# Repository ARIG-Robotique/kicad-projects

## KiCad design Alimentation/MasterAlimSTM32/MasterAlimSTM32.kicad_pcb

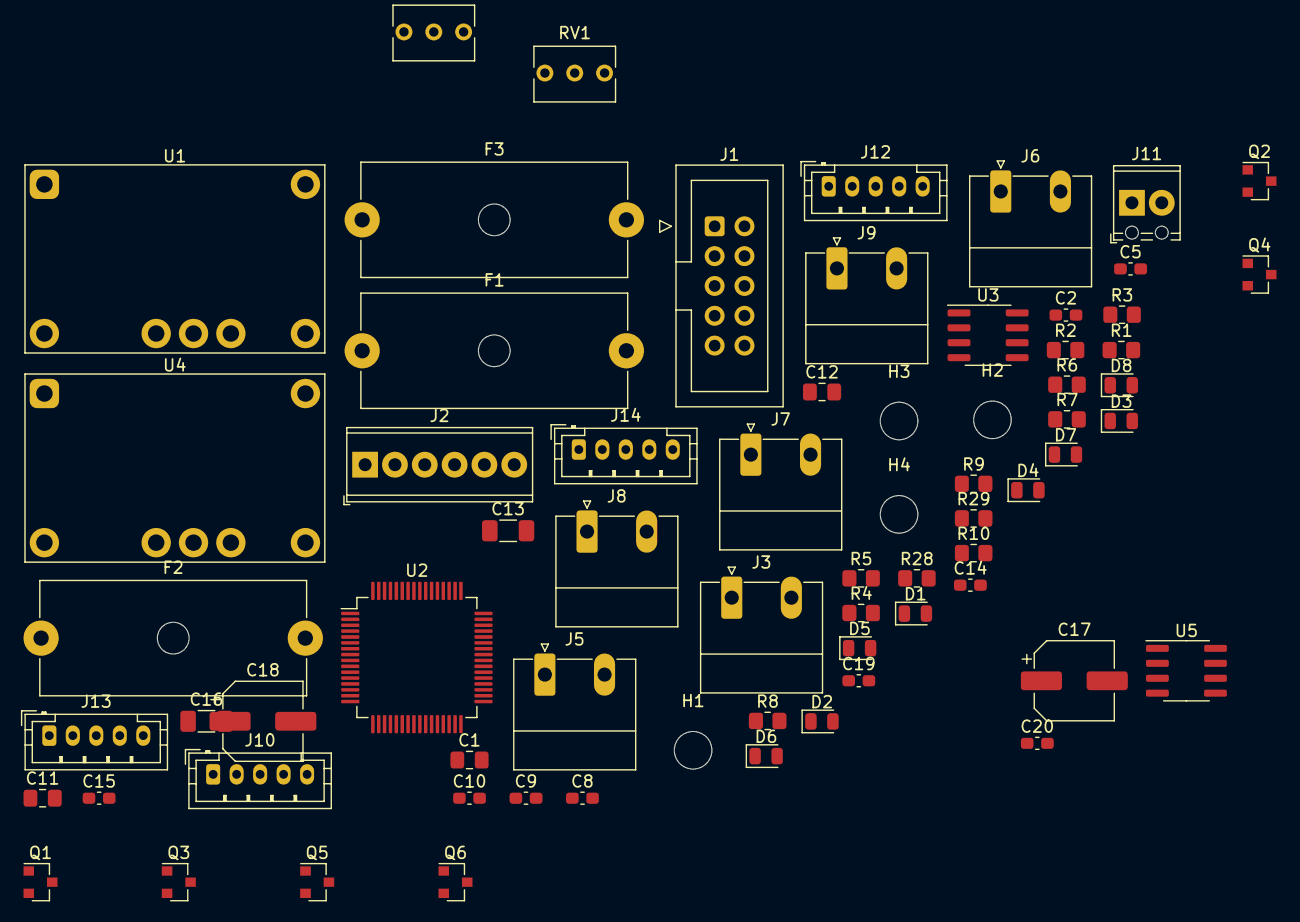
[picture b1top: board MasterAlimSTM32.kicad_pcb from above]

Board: 2 copper layers, 69 parts (0 on the bottom side), 39 nets, no tracks yet.

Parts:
C1: 4.7u; C_0805_2012Metric_Pad1.18x1.45mm_HandSolder
C2, C5, C8, C9, C10, C15, C20: 100n; C_0603_1608Metric_Pad1.08x0.95mm_HandSolder
C11, C12: 2.2u; C_0805_2012Metric_Pad1.18x1.45mm_HandSolder
C13, C16: 2.2u; C_1206_3216Metric_Pad1.33x1.80mm_HandSolder
C14, C19: 1n; C_0603_1608Metric_Pad1.08x0.95mm_HandSolder
C17, C18: 100u; CP_Elec_6.3x5.4
D1: AU; LED_0805_2012Metric
D2: 5V; LED_0805_2012Metric
D3: T1; LED_0805_2012Metric
D4: T2; LED_0805_2012Metric
D5: T3; LED_0805_2012Metric
D6: T4; LED_0805_2012Metric
D7: 3.3V; LED_0805_2012Metric
D8: Heart Beat; LED_0805_2012Metric
F1: 10A; Fuseholder_Cylinder-5x20mm_Schurter_0031_8201_Horizontal_Op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
F2, F3: 3A; Fuseholder_Cylinder-5x20mm_Schurter_0031_8201_Horizontal_Op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
H1, H2, H3, H4: MountingHole; MountingHole_3.2mm_M3
J1: Ext-Con; IDC-Header_2x05_P2.54mm_Vertical
J2: 5V; TerminalBlock_Phoenix_MPT-0,5-6-2.54_1x06_P2.54mm_Horizontal
J3: Bat. IN; PhoenixContact_MC_1,5_2-G-5.08_1x02_P5.08mm_Horizontal
J5: Direct Out; PhoenixContact_MC_1,5_2-G-5.08_1x02_P5.08mm_Horizontal
J6: Reg 1; PhoenixContact_MC_1,5_2-G-5.08_1x02_P5.08mm_Horizontal
J7: Reg 2; PhoenixContact_MC_1,5_2-G-5.08_1x02_P5.08mm_Horizontal
J8: Reg 3; PhoenixContact_MC_1,5_2-G-5.08_1x02_P5.08mm_Horizontal
J9: Reg 4; PhoenixContact_MC_1,5_2-G-5.08_1x02_P5.08mm_Horizontal
J10: Interf-Reg1; JST_PH_B5B-PH-K_1x05_P2.00mm_Vertical
J11: AU Logic; TerminalBlock_Phoenix_MPT-0,5-2-2.54_1x02_P2.54mm_Horizontal
J12: Interf-Reg2; JST_PH_B5B-PH-K_1x05_P2.00mm_Vertical
J13: Interf-Reg3; JST_PH_B5B-PH-K_1x05_P2.00mm_Vertical
J14: Interf-Reg4; JST_PH_B5B-PH-K_1x05_P2.00mm_Vertical
Q1, Q2, Q3, Q4, Q5, Q6: BSS138; SOT-23
R1, R8: 10k; R_0805_2012Metric_Pad1.20x1.40mm_HandSolder
R2: 220; R_0805_2012Metric_Pad1.20x1.40mm_HandSolder
R3: 280; R_0805_2012Metric_Pad1.20x1.40mm_HandSolder
R4, R5, R6, R7: 180; R_0805_2012Metric_Pad1.20x1.40mm_HandSolder
R9: 150; R_0805_2012Metric_Pad1.20x1.40mm_HandSolder
R10: 1k5; R_0805_2012Metric_Pad1.20x1.40mm_HandSolder
R28: 820k; R_0805_2012Metric_Pad1.20x1.40mm_HandSolder
R29: 130k; R_0805_2012Metric_Pad1.20x1.40mm_HandSolder
RV1, RV2: 1M; Potentiometer_Bourns_3266Y_Vertical
U1, U4: PTN78060W_EUW-7; Texas_EUW_R-PDSS-T7_THT
U2: STM32F405RGTx; LQFP-64_10x10mm_P0.5mm
U3, U5: ACS712xLCTR-20A; SOIC-8_3.9x4.9mm_P1.27mm

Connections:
+3V3: C1.1, C2.2, C5.2, C8.2, C9.2, C10.2, F3.2, J1.3, J2.3, J2.4, Q1.1, Q2.1, Q3.1, Q4.1, Q5.1, Q6.1, R1.1, R2.1, R4.1, R5.1, R6.1, R7.1, R9.1, U2.1, U2.19, U2.32, U2.48, U2.64
+5V: C15.2, C20.2, F2.1, J1.1, J2.1, J2.2, J10.1, J12.1, J13.1, J14.1, R3.1, U3.8, U5.8
+BATT: C13.1, C16.1, F1.1, J5.2, J6.2, J7.2, J8.2, J9.2, RV1.1, RV2.1, U1.2, U4.2
/ANA_BAT_VOLT_5: R28.2, R29.1
/AU_33: D1.1, J11.1, R1.2, U2.41
/BAT_IN: F1.2, R28.1, U3.3, U3.4
/BOOT0: R8.1, U2.60
/EN_T1_5: J10.2, Q3.3
/EN_T1_33: D3.1, Q3.2, U2.33
/EN_T2_5: J12.2, Q4.3
/EN_T2_33: D4.1, Q4.2, U2.34
/EN_T3_5: J13.2, Q5.3
/EN_T3_33: D5.1, Q5.2, U2.35
/EN_T4_5: J14.2, Q6.3
/EN_T4_33: D6.1, Q6.2, U2.36
/HEART_BEAT_33: D8.2, U2.43
/SCL_5: J1.10, Q1.3
/SCL_33: J1.8, Q1.2, U2.58
/SDA_5: J1.9, Q2.3
/SDA_33: J1.7, Q2.2, U2.59
/VO_5: C17.1, U1.5, U1.6, U5.1, U5.2
GND: C1.2, C2.1, C5.1, C8.1, C9.1, C10.1, C11.2, C12.2, C13.2, C14.2, C15.1, C16.2, C17.2, C18.2, C19.2, C20.1, D2.1, D7.1, J1.2, J1.4, J2.5, J2.6, J3.1, J5.1, J6.1, J7.1, J8.1, J9.1, J10.5, J11.2, J12.5, J13.5, J14.5, R10.2, R29.2, RV1.3, RV2.3, U1.1, U1.7, U2.12, U2.18, U2.63, U3.5, U4.1, U4.7, U5.5
unnamed: C11.1, U2.31
unnamed: C12.1, U2.47
unnamed: C14.1, U3.6
unnamed: C18.1, F3.1, U4.5, U4.6
unnamed: C19.1, U5.6
unnamed: D1.2, R2.2
unnamed: D2.2, R3.2
unnamed: D3.2, R4.2
unnamed: D4.2, R5.2
unnamed: D5.2, R6.2
unnamed: D6.2, R7.2
unnamed: D7.2, R9.2
unnamed: D8.1, R10.1
unnamed: F2.2, U5.3, U5.4
unnamed: J3.2, U3.1, U3.2
unnamed: RV1.2, U1.4
unnamed: RV2.2, U4.4

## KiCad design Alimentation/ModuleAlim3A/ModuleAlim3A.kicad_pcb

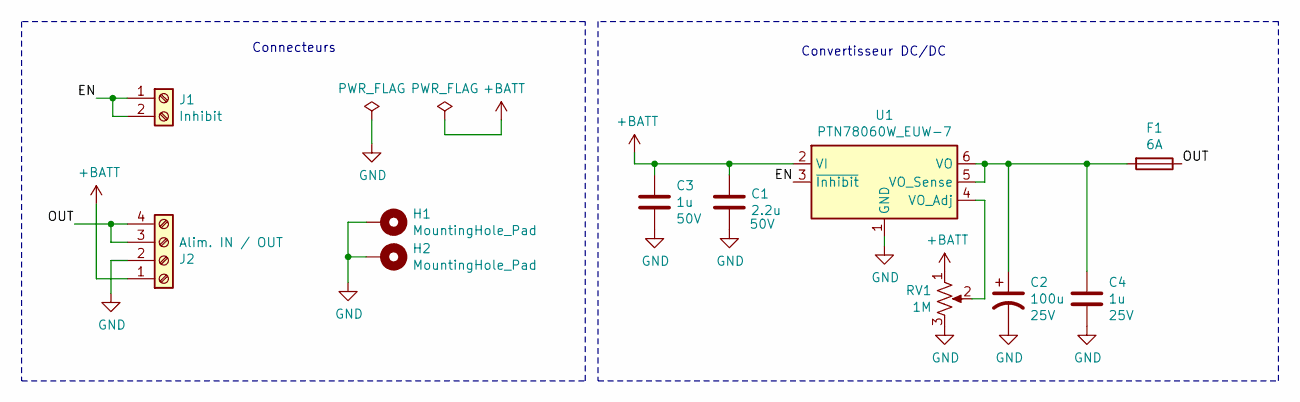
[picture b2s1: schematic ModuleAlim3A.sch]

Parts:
C1: 2.2u; C_1206_3216Metric_Pad1.33x1.80mm_HandSolder; LCSC Part C50254
C2: 100u; CP_Elec_6.3x7.7; LCSC Part C176675
C3: 1u; C_0805_2012Metric_Pad1.18x1.45mm_HandSolder; LCSC Part C28323
C4: 1u; C_0402_1005Metric_Pad0.74x0.62mm_HandSolder; LCSC Part C52923
F1: 6A; Fuseholder_Cylinder-5x20mm_Schurter_0031_8201_Horizontal_Op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; JLCPCB BOM 0
H1, H2: MountingHole_Pad; MountingHole_3.2mm_M3_Pad_Via; JLCPCB BOM 0
J1: Inhibit; TerminalBlock_Phoenix_MPT-0,5-2-2.54_1x02_P2.54mm_Horizontal; JLCPCB BOM 0
J2: Alim. IN / OUT; TerminalBlock_Phoenix_MKDS-1,5-4-5.08_1x04_P5.08mm_Horizont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; JLCPCB BOM 0
RV1: 1M; Potentiometer_Bourns_3296W_Vertical; JLCPCB BOM 0
U1: PTN78060W_EUW-7; Texas_EUW_R-PDSS-T7_THT; JLCPCB BOM 0

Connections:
+BATT: C1.1, C3.1, J2.1, RV1.1, U1.2 (VI)
/EN: J1.1, J1.2, U1.3 (~Inhibit)
/OUT: F1.1, J2.3, J2.4
GND: C1.2, C2.2, C3.2, C4.2, H1.1, H2.1, J2.2, RV1.3, U1.1 (GND), U1.7 (GND)
unnamed: C2.1, C4.1, F1.2, U1.5 (VO_Sense), U1.6 (VO)
unnamed: RV1.2, U1.4 (VO_Adj)

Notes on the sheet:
Convertisseur DC/DC
Connecteurs

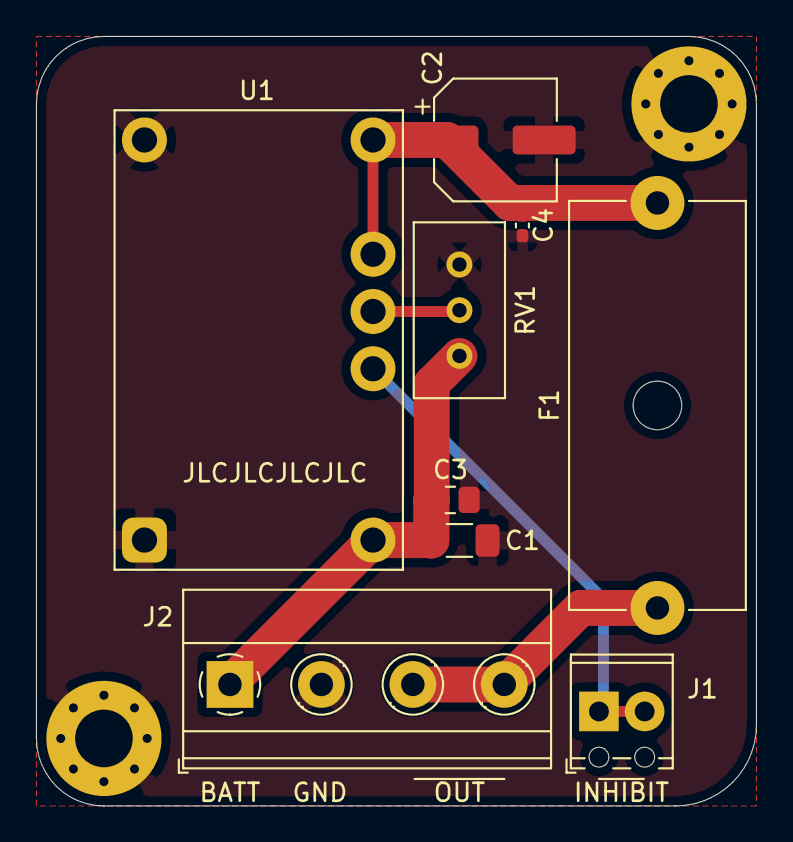
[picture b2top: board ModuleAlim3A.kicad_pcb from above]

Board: 2 copper layers, 40.0 x 42.8 mm, 11 parts (0 on the bottom side), 6 nets.

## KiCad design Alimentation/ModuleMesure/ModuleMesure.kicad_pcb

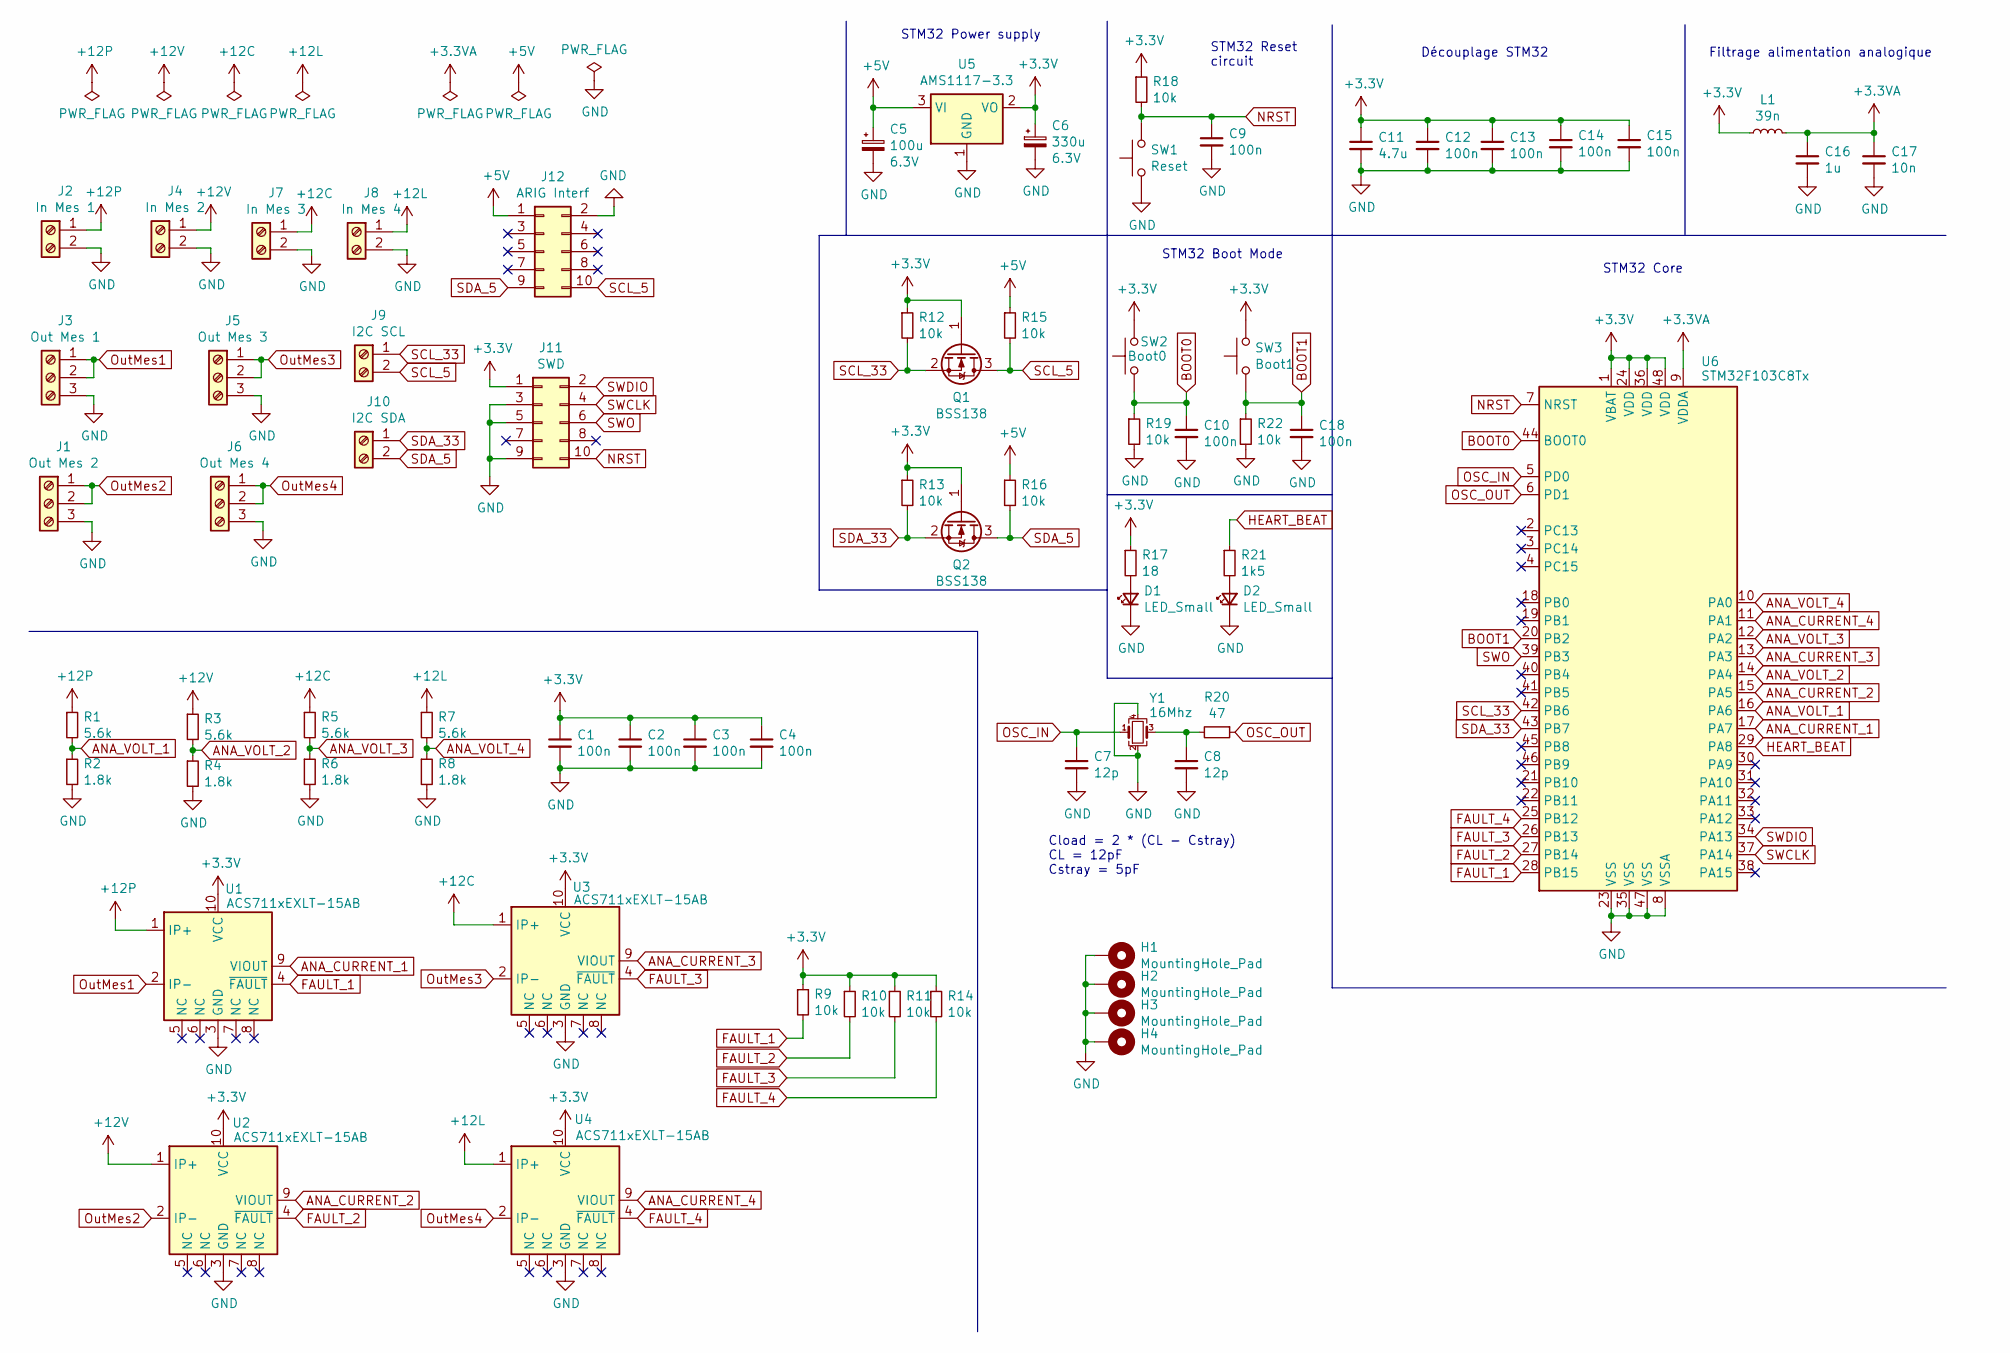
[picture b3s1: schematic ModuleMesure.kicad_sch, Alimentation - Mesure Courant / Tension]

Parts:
C1, C2, C3, C4, C9, C10, C12, C13, C14, C15, C18: 100n; C_0402_1005Metric_Pad0.74x0.62mm_HandSolder; LCSC Part C541405
C5: 100u; CP_Elec_5x5.4; LCSC Part C72472
C6: 330u; CP_Elec_6.3x7.7; LCSC Part C58276
C7, C8: 12p; C_0402_1005Metric_Pad0.74x0.62mm_HandSolder
C11: 4.7u; C_0402_1005Metric_Pad0.74x0.62mm_HandSolder; LCSC Part C87147
C16: 1u; C_0402_1005Metric_Pad0.74x0.62mm_HandSolder; LCSC Part C87144
C17: 10n; C_0402_1005Metric_Pad0.74x0.62mm_HandSolder; LCSC Part C309453
D1, D2: LED_Small; LED_0805_2012Metric_Pad1.15x1.40mm_HandSolder
H1, H2, H3, H4: MountingHole_Pad; MountingHole_3.2mm_M3_Pad_Via
J1: Out Mes 2; TerminalBlock_Phoenix_MKDS-1,5-3-5.08_1x03_P5.08mm_Horizont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
J2: In Mes 1; TerminalBlock_Phoenix_MKDS-1,5-2-5.08_1x02_P5.08mm_Horizont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
J3: Out Mes 1; TerminalBlock_Phoenix_MKDS-1,5-3-5.08_1x03_P5.08mm_Horizont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
J4: In Mes 2; TerminalBlock_Phoenix_MKDS-1,5-2-5.08_1x02_P5.08mm_Horizont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
J5: Out Mes 3; TerminalBlock_Phoenix_MKDS-1,5-3-5.08_1x03_P5.08mm_Horizont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
J6: Out Mes 4; TerminalBlock_Phoenix_MKDS-1,5-3-5.08_1x03_P5.08mm_Horizont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
J7: In Mes 3; TerminalBlock_Phoenix_MKDS-1,5-2-5.08_1x02_P5.08mm_Horizont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
J8: In Mes 4; TerminalBlock_Phoenix_MKDS-1,5-2-5.08_1x02_P5.08mm_Horizont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
J9: I2C SCL; TerminalBlock_Phoenix_MPT-0,5-2-2.54_1x02_P2.54mm_Horizontal
J10: I2C SDA; TerminalBlock_Phoenix_MPT-0,5-2-2.54_1x02_P2.54mm_Horizontal
J11: SWD; PinHeader_2x05_P1.27mm_Vertical_SMD
J12: ARIG Interf; IDC-Header_2x05_P2.54mm_Vertical
L1: 39n; L_0402_1005Metric_Pad0.77x0.64mm_HandSolder
Q1, Q2: BSS138; SOT-23
R1, R3, R5, R7: 5.6k; R_0805_2012Metric_Pad1.20x1.40mm_HandSolder
R2, R4, R6, R8: 1.8k; R_0805_2012Metric_Pad1.20x1.40mm_HandSolder
R9, R10, R11, R12, R13, R14, R15, R16, R18, R19, R22: 10k; R_0805_2012Metric_Pad1.20x1.40mm_HandSolder
R17: 18; R_0805_2012Metric_Pad1.20x1.40mm_HandSolder
R20: 47; R_0402_1005Metric_Pad0.72x0.64mm_HandSolder
R21: 1k5; R_0805_2012Metric_Pad1.20x1.40mm_HandSolder
SW1: Reset; SW_SPST_B3U-1000P; LCSC Part C231329
SW2: Boot0; SW_SPST_B3U-1000P; LCSC Part C231329
SW3: Boot1; SW_SPST_B3U-1000P; LCSC Part C231329
U1, U2, U3, U4: ACS711xEXLT-15AB; Allegro_QFN-12-10-1EP_3x3mm_P0.5mm; LCSC Part C150824
U5: AMS1117-3.3; SOT-223-3_TabPin2
U6: STM32F103C8Tx; LQFP-48_7x7mm_P0.5mm; LCSC Part C8734
Y1: 16Mhz; Crystal_SMD_3225-4Pin_3.2x2.5mm_HandSoldering; LCSC Part C13738

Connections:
+3.3VA: C16.1, C17.1, L1.2, U6.9 (VDDA)
+3V3: C1.1, C2.1, C3.1, C4.1, C6.1, C11.1, C12.1, C13.1, C14.1, C15.1, J11.1, L1.1, Q1.1 (G), Q2.1 (G), R9.1, R10.1, R11.1, R12.1, R13.1, R14.1, R17.1, R18.1, SW2.2, SW3.2, U1.10 (VCC), U2.10 (VCC), U3.10 (VCC), U4.10 (VCC), U5.2 (VO), U6.1 (VBAT), U6.24 (VDD), U6.36 (VDD), U6.48 (VDD)
+5V: C5.1, J12.1, R15.1, R16.1, U5.3 (VI)
+12C: J7.1, R5.1, U3.1 (IP+)
+12L: J8.1, R7.1, U4.1 (IP+)
+12P: J2.1, R1.1, U1.1 (IP+)
+12V: J4.1, R3.1, U2.1 (IP+)
ANA_CURRENT_1: U1.9 (VIOUT), U6.17 (PA7)
ANA_CURRENT_2: U2.9 (VIOUT), U6.15 (PA5)
ANA_CURRENT_3: U3.9 (VIOUT), U6.13 (PA3)
ANA_CURRENT_4: U4.9 (VIOUT), U6.11 (PA1)
ANA_VOLT_1: R1.2, R2.1, U6.16 (PA6)
ANA_VOLT_2: R3.2, R4.1, U6.14 (PA4)
ANA_VOLT_3: R5.2, R6.1, U6.12 (PA2)
ANA_VOLT_4: R7.2, R8.1, U6.10 (PA0)
BOOT0: C10.1, R19.1, SW2.1, U6.44 (BOOT0)
BOOT1: C18.1, R22.1, SW3.1, U6.20 (PB2)
FAULT_1: R9.2, U1.4 (~FAULT), U6.28 (PB15)
FAULT_2: R10.2, U2.4 (~FAULT), U6.27 (PB14)
FAULT_3: R11.2, U3.4 (~FAULT), U6.26 (PB13)
FAULT_4: R14.2, U4.4 (~FAULT), U6.25 (PB12)
GND: C1.2, C2.2, C3.2, C4.2, C5.2, C6.2, C7.2, C8.2, C9.2, C10.2, C11.2, C12.2, C13.2, C14.2, C15.2, C16.2, C17.2, C18.2, D1.1 (K), D2.1 (K), H1.1, H2.1, H3.1, H4.1, J1.3, J2.2, J3.3, J4.2, J5.3, J6.3, J7.2, J8.2, J11.3, J11.5, J11.9, J12.2, R2.2, R4.2, R6.2, R8.2, R19.2, R22.2, SW1.1, U1.3 (GND), U2.3 (GND), U3.3 (GND), U4.3 (GND), U5.1 (GND), U6.8 (VSSA), U6.23 (VSS), U6.35 (VSS), U6.47 (VSS), Y1.2, Y1.4
HEART_BEAT: R21.1, U6.29 (PA8)
NRST: C9.1, J11.10, R18.2, SW1.2, U6.7 (NRST)
unnamed: C8.1, R20.2, Y1.3
unnamed: D1.2 (A), R17.2
unnamed: D2.2 (A), R21.2
OSC_IN: C7.1, U6.5 (PD0), Y1.1
OSC_OUT: R20.1, U6.6 (PD1)
OutMes1: J3.1, J3.2, U1.2 (IP-)
OutMes2: J1.1, J1.2, U2.2 (IP-)
OutMes3: J5.1, J5.2, U3.2 (IP-)
OutMes4: J6.1, J6.2, U4.2 (IP-)
SCL_5: J9.2, J12.10, Q1.3 (D), R15.2
SCL_33: J9.1, Q1.2 (S), R12.2, U6.42 (PB6)
SDA_5: J10.2, J12.9, Q2.3 (D), R16.2
SDA_33: J10.1, Q2.2 (S), R13.2, U6.43 (PB7)
SWCLK: J11.4, U6.37 (PA14)
SWDIO: J11.2, U6.34 (PA13)
SWO: J11.6, U6.39 (PB3)

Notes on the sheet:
STM32 Boot Mode
Filtrage alimentation analogique
STM32 Core
STM32 Reset circuit
Cload = 2 * (CL - Cstray) CL = 12pF Cstray = 5pF
STM32 Power supply
Découplage STM32

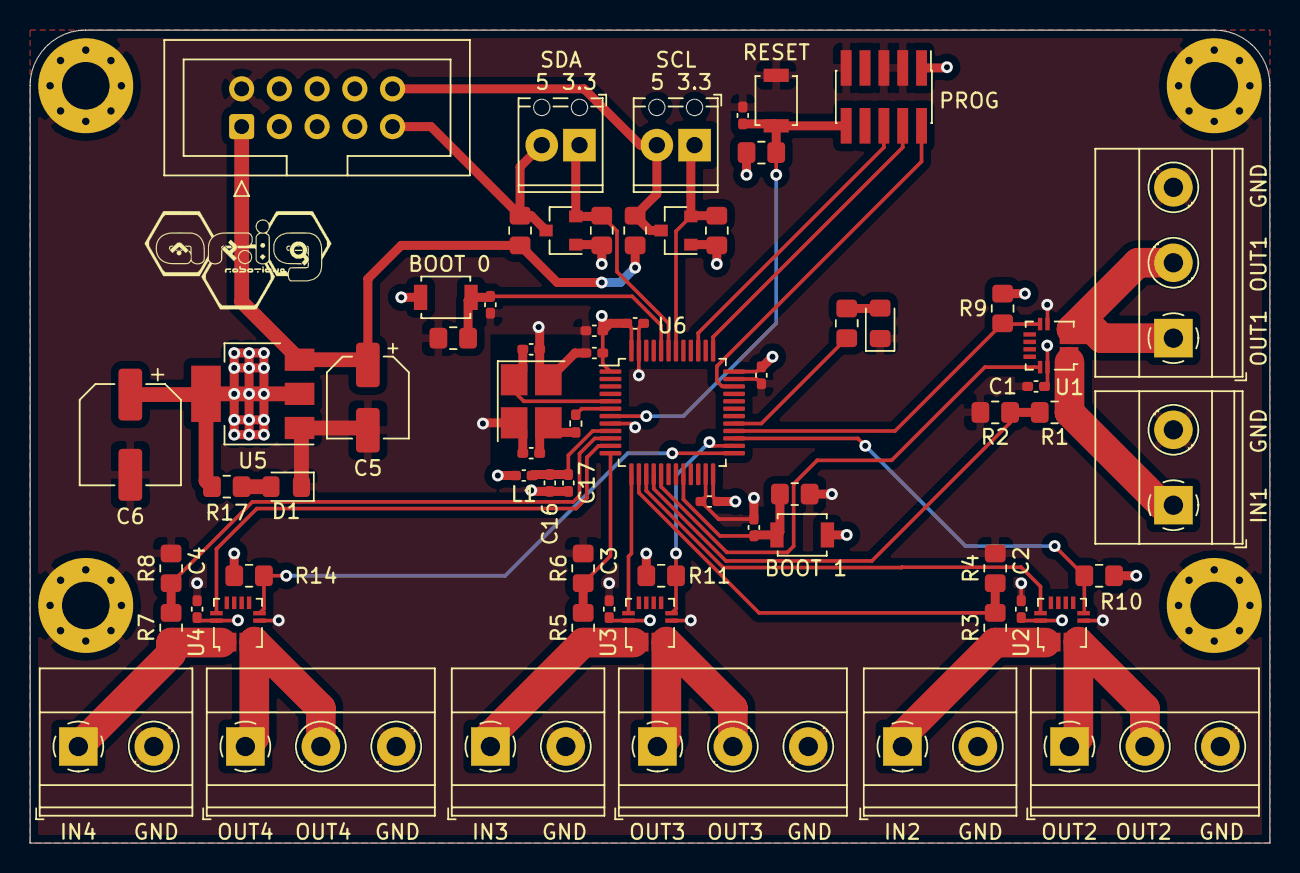
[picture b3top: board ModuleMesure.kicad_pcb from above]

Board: 4 copper layers, 83.5 x 54.8 mm, 71 parts (0 on the bottom side), 40 nets.

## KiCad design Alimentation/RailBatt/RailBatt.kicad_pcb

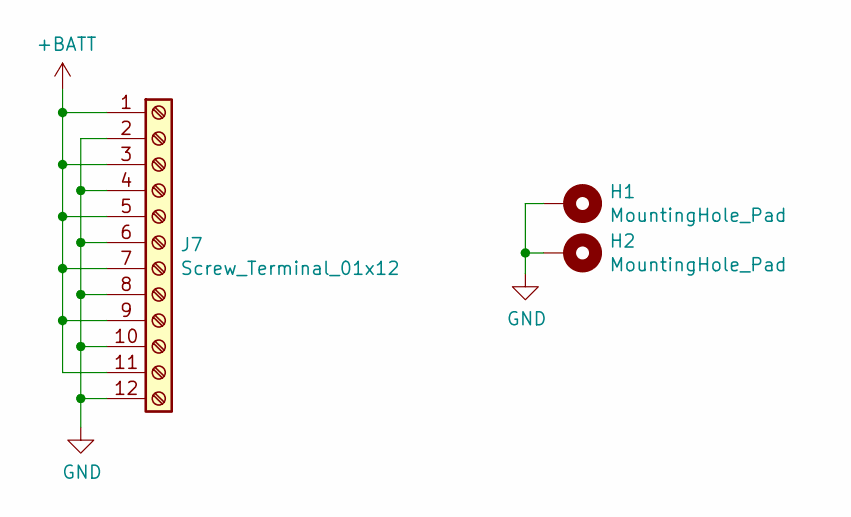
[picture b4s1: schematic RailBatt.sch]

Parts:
H1, H2: MountingHole_Pad; MountingHole_3.2mm_M3_Pad_Via
J7: Screw_Terminal_01x12; TerminalBlock_Phoenix_MKDS-1,5-12-5.08_1x12_P5.08mm_Horizon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

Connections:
+BATT: J7.1, J7.3, J7.5, J7.7, J7.9, J7.11
GND: H1.1, H2.1, J7.2, J7.4, J7.6, J7.8, J7.10, J7.12

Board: 2 copper layers, 3 parts (0 on the bottom side), 2 nets, no tracks yet.

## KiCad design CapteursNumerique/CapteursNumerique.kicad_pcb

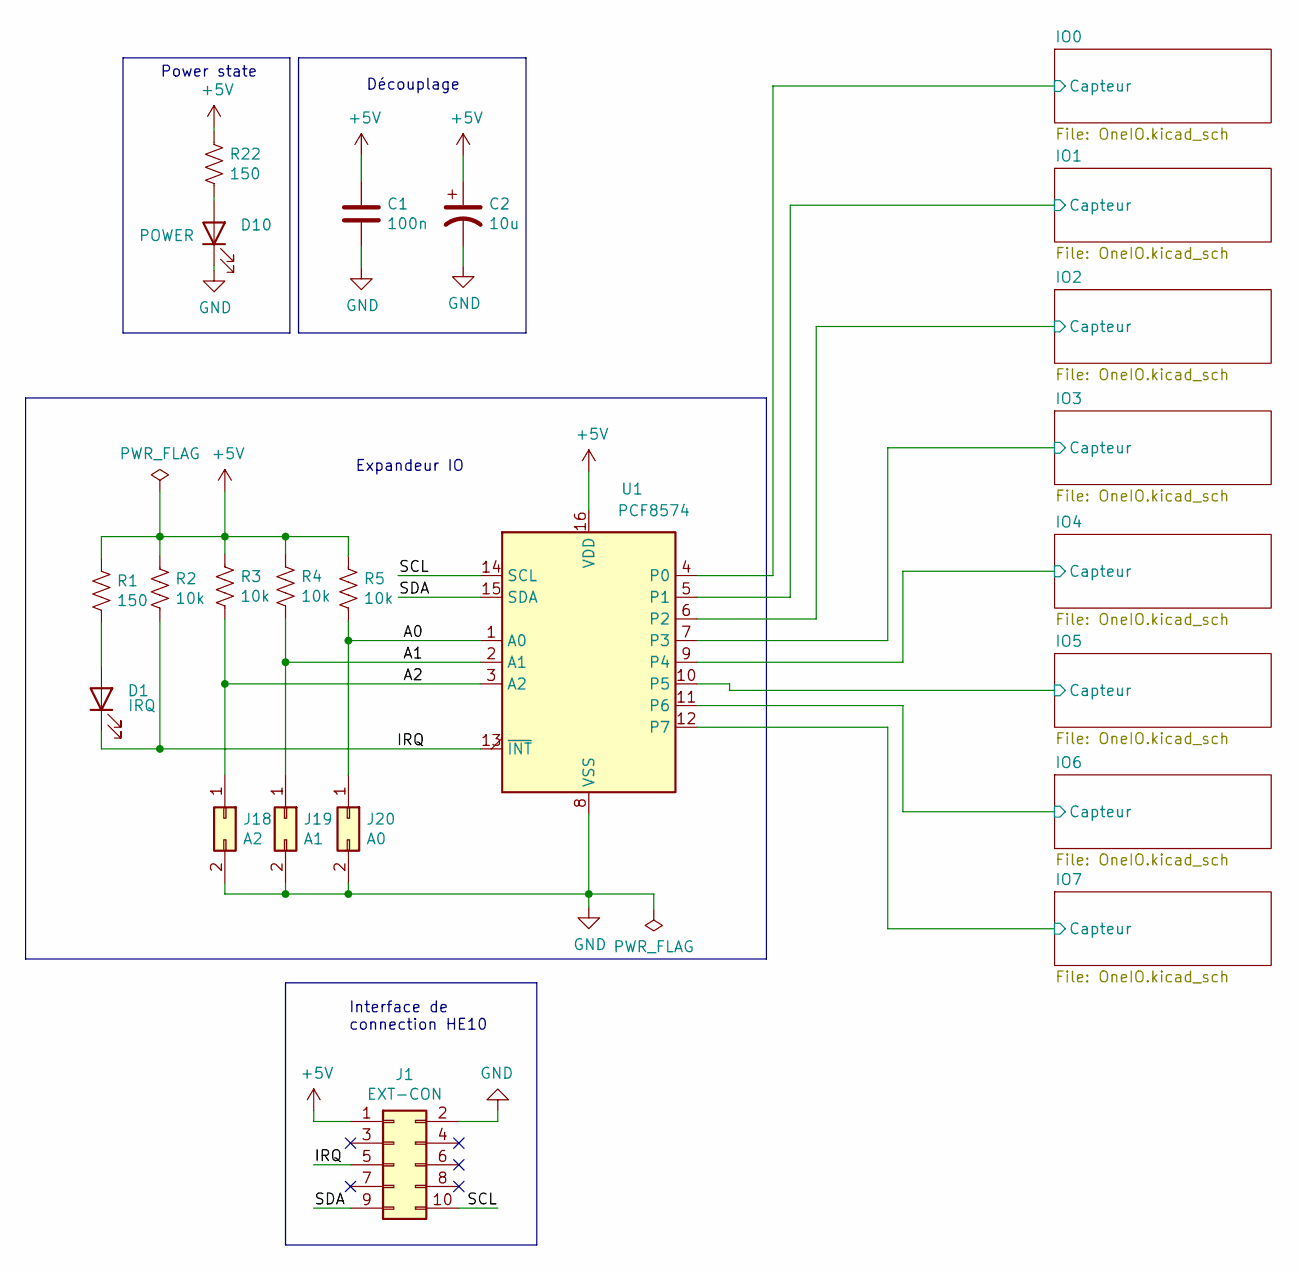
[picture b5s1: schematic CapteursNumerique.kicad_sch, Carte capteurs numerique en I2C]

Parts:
C1: 100n; C_0805_2012Metric_Pad1.18x1.45mm_HandSolder; LCSC Part C28233
C2: 10u; CP_Elec_4x5.4; LCSC Part C134721
D1: IRQ; LED_0805_2012Metric_Pad1.15x1.40mm_HandSolder; LCSC Part C72037
D10: POWER; LED_0805_2012Metric_Pad1.15x1.40mm_HandSolder; LCSC Part C63855
J1: EXT-CON; IDC-Header_2x05_P2.54mm_Vertical; JLCPCB BOM 0
J18: A2; SolderJumper-2_P1.3mm_Open_Pad1.0x1.5mm; JLCPCB BOM 0
J19: A1; SolderJumper-2_P1.3mm_Open_Pad1.0x1.5mm; JLCPCB BOM 0
J20: A0; SolderJumper-2_P1.3mm_Open_Pad1.0x1.5mm; JLCPCB BOM 0
R1, R22: 150; R_0805_2012Metric_Pad1.20x1.40mm_HandSolder; LCSC Part C17471
R2, R3, R4, R5: 10k; R_0805_2012Metric_Pad1.20x1.40mm_HandSolder; LCSC Part C17414
U1: PCF8574; SOIC-16W_7.5x10.3mm_P1.27mm; LCSC Part C7605

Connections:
+5V: C1.1, C2.1, J1.1, R1.1, R2.1, R3.1, R4.1, R5.1, R22.1, U1.16 (VDD); also elsewhere on the board
/A0: J20.1, R5.2, U1.1 (A0)
/A1: J19.1, R4.2, U1.2 (A1)
/A2: J18.1, R3.2, U1.3 (A2)
/IO0/Capteur: U1.4 (P0); also elsewhere on the board
/IO1/Capteur: U1.5 (P1); also elsewhere on the board
/IO2/Capteur: U1.6 (P2); also elsewhere on the board
/IO3/Capteur: U1.7 (P3); also elsewhere on the board
/IO4/Capteur: U1.9 (P4); also elsewhere on the board
/IO5/Capteur: U1.10 (P5); also elsewhere on the board
/IO6/Capteur: U1.11 (P6); also elsewhere on the board
/IO7/Capteur: U1.12 (P7); also elsewhere on the board
/IRQ: D1.1 (K), J1.5, R2.2, U1.13 (~INT)
/SCL: J1.10, U1.14 (SCL)
/SDA: J1.9, U1.15 (SDA)
GND: C1.2, C2.2, D10.1 (K), J1.2, J18.2, J19.2, J20.2, U1.8 (VSS); also elsewhere on the board
unnamed: D1.2 (A), R1.2
unnamed: D10.2 (A), R22.2

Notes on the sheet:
Interface de connection HE10
Expandeur IO
Power state
Découplage

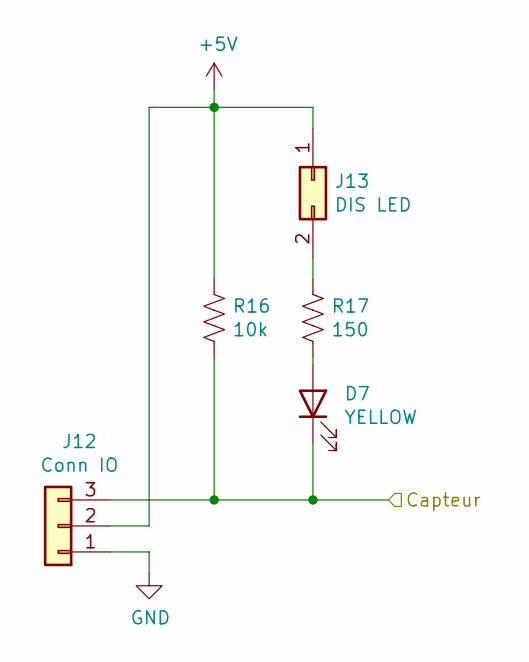
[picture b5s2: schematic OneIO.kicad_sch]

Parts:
D7: YELLOW; LED_0805_2012Metric_Pad1.15x1.40mm_HandSolder; LCSC Part C74346
J12: Conn IO; PinHeader_1x03_P2.54mm_Vertical; JLCPCB BOM 0
J13: DIS LED; SolderJumper-2_P1.3mm_Open_Pad1.0x1.5mm; JLCPCB BOM 0
R16: 10k; R_0805_2012Metric_Pad1.20x1.40mm_HandSolder; LCSC Part C17414
R17: 150; R_0805_2012Metric_Pad1.20x1.40mm_HandSolder; LCSC Part C17471

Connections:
+5V: J12.2, J13.1, R16.1; also elsewhere on the board
/IO1/Capteur: D7.1 (K), J12.3, R16.2; also elsewhere on the board
GND: J12.1; also elsewhere on the board
unnamed: D7.2 (A), R17.2
unnamed: J13.2, R17.1

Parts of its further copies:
D2, D3, D4, D5, D6, D8, D9: YELLOW; LED_0805_2012Metric_Pad1.15x1.40mm_HandSolder; LCSC Part C74346
J2, J4, J6, J8, J10, J14, J16: Conn IO; PinHeader_1x03_P2.54mm_Vertical; JLCPCB BOM 0
J3, J5, J7, J9, J11, J15, J17: DIS LED; SolderJumper-2_P1.3mm_Open_Pad1.0x1.5mm; JLCPCB BOM 0
R6, R8, R10, R12, R14, R18, R20: 10k; R_0805_2012Metric_Pad1.20x1.40mm_HandSolder; LCSC Part C17414
R7, R9, R11, R13, R15, R19, R21: 150; R_0805_2012Metric_Pad1.20x1.40mm_HandSolder; LCSC Part C17471

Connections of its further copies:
+5V: J2.2, J3.1, J4.2, J5.1, J6.2, J7.1, J8.2, J9.1, J10.2, J11.1, J14.2, J15.1, J16.2, J17.1, R6.1, R8.1, R10.1, R12.1, R14.1, R18.1, R20.1; also elsewhere on the board
/IO0/Capteur: D8.1 (K), J14.3, R18.2; also elsewhere on the board
/IO2/Capteur: D2.1 (K), J2.3, R6.2; also elsewhere on the board
/IO3/Capteur: D3.1 (K), J4.3, R8.2; also elsewhere on the board
/IO4/Capteur: D4.1 (K), J6.3, R10.2; also elsewhere on the board
/IO5/Capteur: D5.1 (K), J8.3, R12.2; also elsewhere on the board
/IO6/Capteur: D6.1 (K), J10.3, R14.2; also elsewhere on the board
/IO7/Capteur: D9.1 (K), J16.3, R20.2; also elsewhere on the board
GND: J2.1, J4.1, J6.1, J8.1, J10.1, J14.1, J16.1; also elsewhere on the board
unnamed: D2.2 (A), R7.2
unnamed: D3.2 (A), R9.2
unnamed: D4.2 (A), R11.2
unnamed: D5.2 (A), R13.2
unnamed: D6.2 (A), R15.2
unnamed: D8.2 (A), R19.2
unnamed: D9.2 (A), R21.2
unnamed: J3.2, R7.1
unnamed: J5.2, R9.1
unnamed: J7.2, R11.1
unnamed: J9.2, R13.1
unnamed: J11.2, R15.1
unnamed: J15.2, R19.1
unnamed: J17.2, R21.1

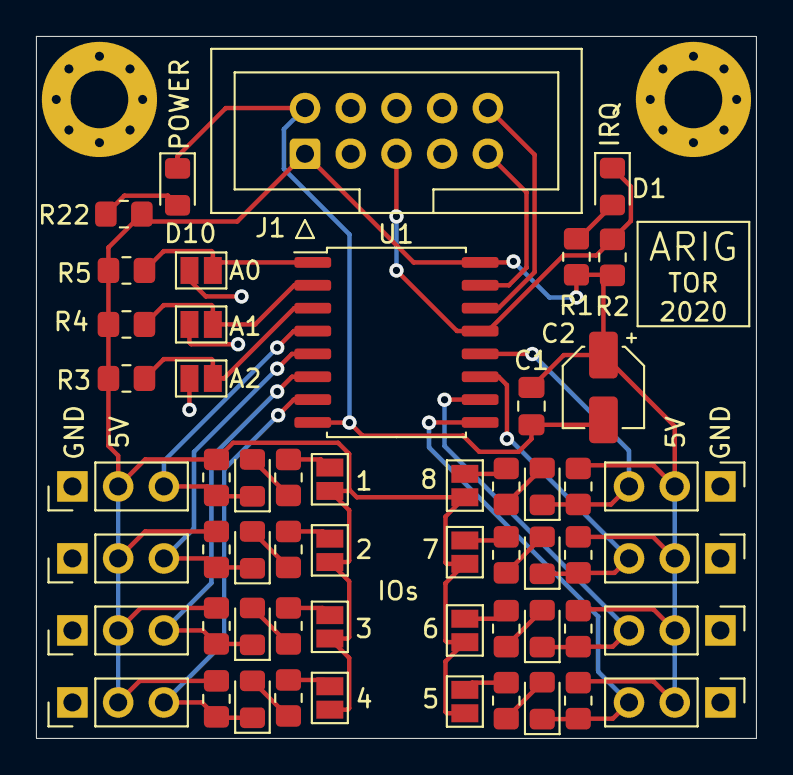
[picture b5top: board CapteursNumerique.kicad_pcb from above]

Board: 2 copper layers, 40.0 x 39.0 mm, 55 parts (0 on the bottom side), 34 nets.
